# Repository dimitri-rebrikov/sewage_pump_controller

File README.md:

# sewage_pump_controller
Electronic controller for sewage pump. Elektronische Steuerung für Abwasserpumpe.

This project implements a simple sewage pump controller.

The project is created using the KiCAD tool.

The advantages of the schematic is the simplicity and that the only one probe is necessary.
The disadvantage is that you need to detect the time the pump needs to emptify the sewage container and then setup this time using the trim pot RV1.

The time formula is 1.1(R3+RV1)C3 and is currently from 5 to 10 sec.
If you need longer time feel free to incerase R3 or RV1 or C3.
If you need shorter time pay attention that the R3 shall not be decreased as otherwise the Q1 which is connected over D1 will stop working in key mode.
Instead just decrease the C3. 

For the power supply I used just a common USB mobile phone charger.

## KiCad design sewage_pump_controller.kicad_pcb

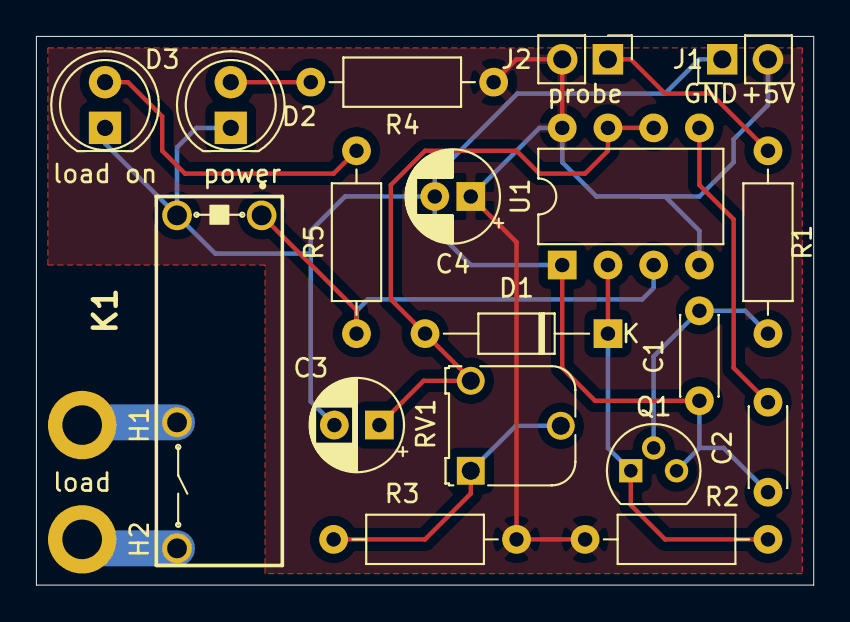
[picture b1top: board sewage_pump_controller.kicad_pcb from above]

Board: 2 copper layers, 43.2 x 30.5 mm, 20 parts (0 on the bottom side), 13 nets.

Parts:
C1, C2: 0.01uF; C_Disc_D4.3mm_W1.9mm_P5.00mm
C3: 50uF; CP_Radial_D5.0mm_P2.50mm
C4: 100uF; CP_Radial_D5.0mm_P2.00mm
D1: BAT43; D_DO-35_SOD27_P10.16mm_Horizontal
D2: Green LED; LED_D5.0mm
D3: Yellow LED; LED_D5.0mm
H1, H2: MountingHole_Pad; MountingHole_2.2mm_M2_DIN965_Pad
J1, J2: Conn_01x02; PinHeader_1x02_P2.54mm_Vertical
K1: HF46F-G-5-HS1T; HF46F
Q1: BC547; TO-92
R1: 3K; R_Axial_DIN0207_L6.3mm_D2.5mm_P10.16mm_Horizontal
R2, R3: 100K; R_Axial_DIN0207_L6.3mm_D2.5mm_P10.16mm_Horizontal
R4, R5: 220; R_Axial_DIN0207_L6.3mm_D2.5mm_P10.16mm_Horizontal
RV1: 100K; Potentiometer_Runtron_RM-065_Vertical
U1: NE555P; DIP-8_W7.62mm

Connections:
+5V: C4.1, J1.2, J2.2, R2.1, R3.1, R4.1, U1.4, U1.8
GND: C1.2, C2.2, C3.2, C4.2, D2.1, D3.1, J1.1, K1.2, Q1.3, U1.1
unnamed: C1.1, Q1.2, R1.2
unnamed: C2.1, U1.5
unnamed: C3.1, D1.2, RV1.3, U1.6, U1.7
unnamed: D1.1, Q1.1, R2.2, U1.2
unnamed: D2.2, R4.2
unnamed: D3.2, R5.2
unnamed: H1.1, K1.3
unnamed: H2.1, K1.4
unnamed: J2.1, R1.1
unnamed: K1.1, R5.1, U1.3
unnamed: R3.2, RV1.1, RV1.2

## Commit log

2021-05-23 fixes typos
2021-05-23 added image to the README file
2021-05-23 added pictures of the PCD and the assembled controller
2021-05-23 added comment about power supply
2021-05-23 added component diagram
